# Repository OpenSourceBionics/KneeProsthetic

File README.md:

# KneeProsthetic

Passive and powered leg prostheses are expensive and require access to specific equipment and technology, making them very inaccessible. Our objective is to build an open source powered prosthesis that is lightweight, inexpensive, and has a functional controller to be a foundation for striving engineers.

## Getting Started

This repository contains the preliminary code to manually control your powered prosthesis through both wired and wireless communication. 

### Prerequisites

* Arduino - latest edition
* Teensyduino - latest edition
* Python 2.7

* Raspberry Pi Zero W (x2 for wireless communication)
* Teensy 4.0

### Installing

* [Teensyduino Download Link](https://www.pjrc.com/teensy/td_download.html)
* [Arduino Download Link](https://www.arduino.cc/en/main/software)

## Running the tests

Explain how to run the  tests for this system

## Authors

* **Justin Francis** - *Initial work* - [jphran](https://github.com/jphran)
* **Palani Thangaraj** - *Initial work* - [palan-thangaraj](https://github.com/palani-thangaraj)

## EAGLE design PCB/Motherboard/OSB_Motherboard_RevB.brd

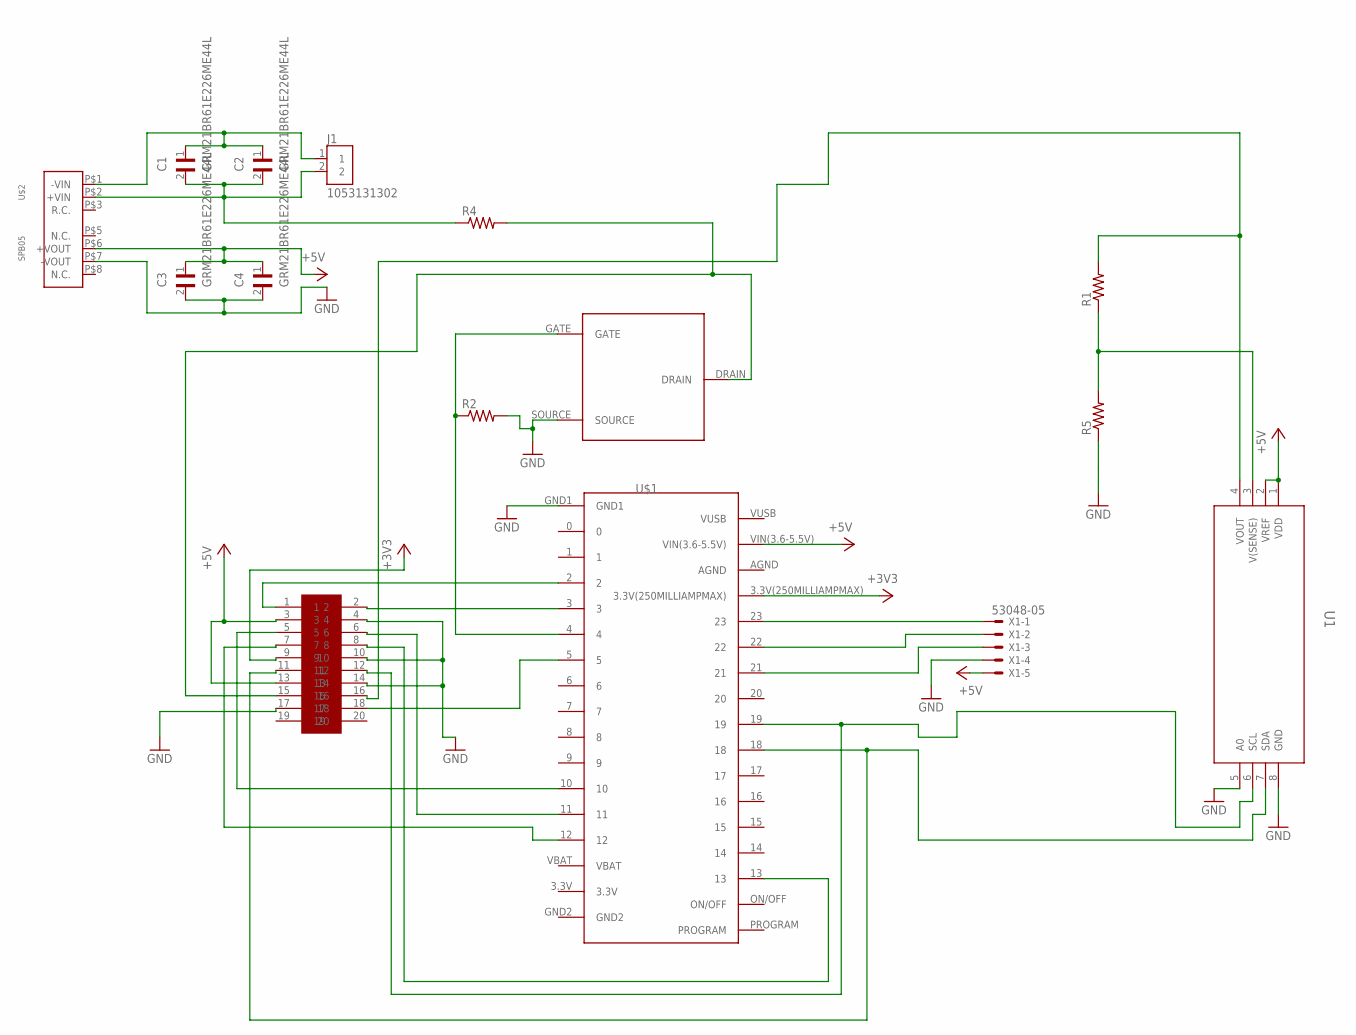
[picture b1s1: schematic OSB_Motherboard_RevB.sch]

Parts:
C1, C2, C3, C4: GRM21BR61E226ME44L; CAPC2012X135N
J1: 1053131302; MOLEX_1053131302
R1, R2, R4, R5: R-US_R0603; R0603
U1: DAC8571IDGKR; DGK8
U$1: TEENSEY4.0
U$2: SPB05; SPB05B-05
U$3: MGSF1N02L
U$4: MOLEX-PICOCLASP-2CIR
X1: 53048-05

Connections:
+3V3: U$1.3.3V(250MILLIAMPMAX), U$4.9
+5V: C3.1, C4.1, U1.1 (VDD), U1.2 (VREF), U$1.VIN(3.6-5.5V), U$2.P$6 (+VOUT), U$4.3, U$4.13, X1.5
GND: C3.2, C4.2, R2.2, R5.1, U1.5 (A0), U1.8 (GND), U$1.GND1, U$2.P$7 (-VOUT), U$3.SOURCE, U$4.4, U$4.10, U$4.14, U$4.17, X1.4
unnamed: U$1.2, U$4.1
unnamed: U$1.23, X1.1
unnamed: U1.6 (SCL), U$1.19, U$4.12
unnamed: U1.7 (SDA), U$1.18, U$4.11
unnamed: U$1.11, U$4.6
unnamed: U$1.3, U$4.2
unnamed: U$1.13, U$4.8
unnamed: U$1.22, X1.2
unnamed: U$1.21, X1.3
unnamed: U$1.12, U$4.7
unnamed: C1.1, C2.1, J1.1, U$2.P$1 (-VIN)
unnamed: U$1.10, U$4.5
unnamed: R1.1, R5.2, U1.3 (V(SENSE))
unnamed: R1.2, U1.4 (VOUT), U$4.16
unnamed: R2.1, U$1.4, U$3.GATE
unnamed: R4.2, U$3.DRAIN, U$4.15
unnamed: C1.2, C2.2, J1.2, R4.1, U$2.P$2 (+VIN)
unnamed: U$1.5, U$4.18

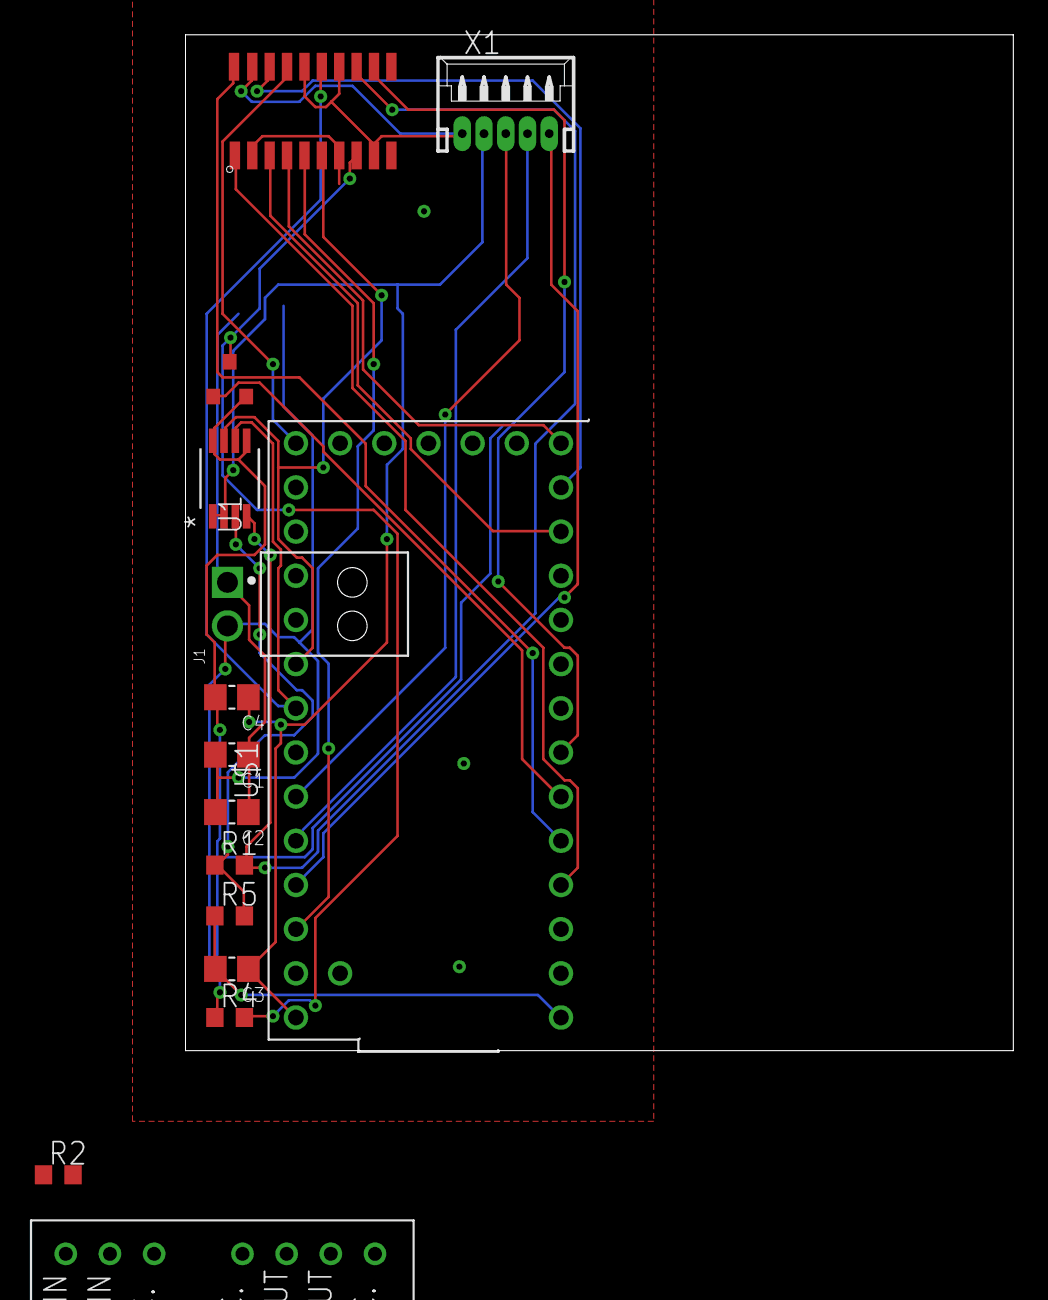
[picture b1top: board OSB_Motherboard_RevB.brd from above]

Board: 2 copper layers, 47.6 x 58.4 mm, 15 parts (0 on the bottom side), 21 nets.

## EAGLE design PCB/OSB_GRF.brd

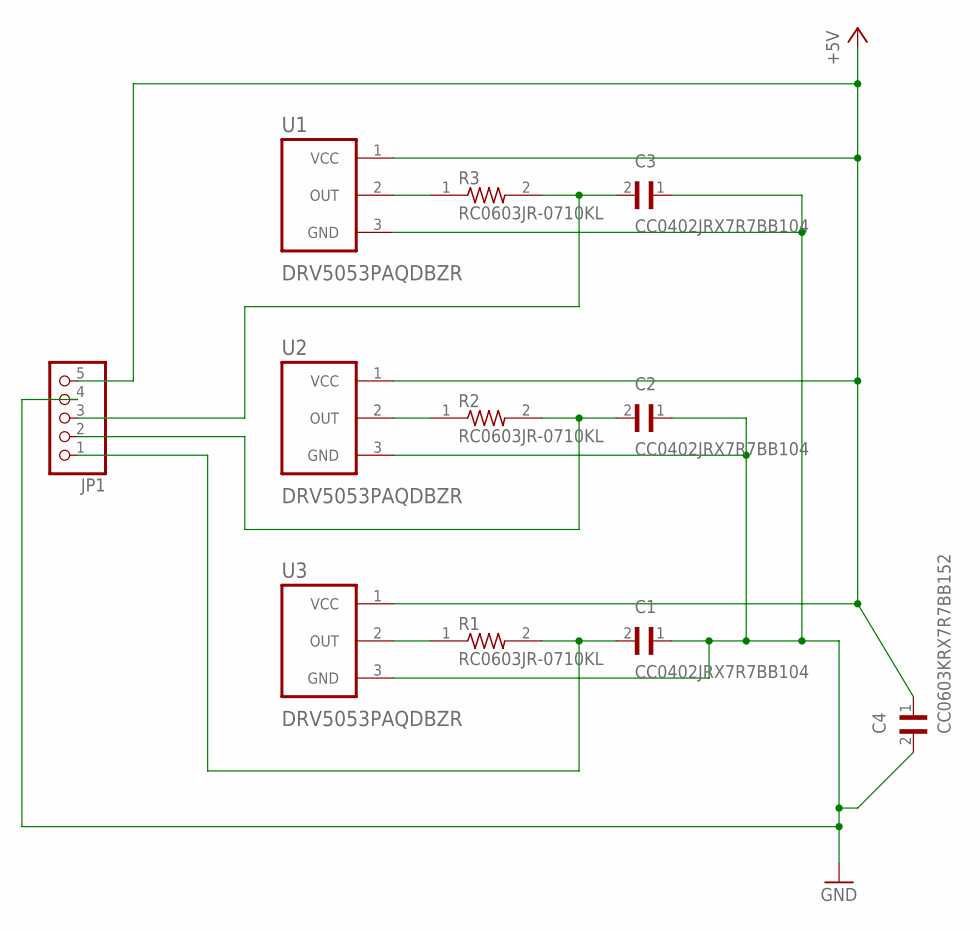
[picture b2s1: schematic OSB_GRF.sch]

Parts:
C1, C2, C3: CC0402JRX7R7BB104; CAPC1005X55N
C4: CC0603KRX7R7BB152; CAPC1608X90
JP1: PINHD-1X55X2MM; 1_05X2MM
R1, R2, R3: RC0603JR-0710KL; RESC1607X60N
U1, U2, U3: DRV5053PAQDBZR; SOT95P237X112-3N

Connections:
+5V: C4.1, JP1.5, U1.1 (VCC), U2.1 (VCC), U3.1 (VCC)
GND: C1.1, C2.1, C3.1, C4.2, JP1.4, U1.3 (GND), U2.3 (GND), U3.3 (GND)
unnamed: R1.1, U3.2 (OUT)
unnamed: R2.1, U2.2 (OUT)
unnamed: R3.1, U1.2 (OUT)
unnamed: C1.2, JP1.1, R1.2
unnamed: C2.2, JP1.2, R2.2
unnamed: C3.2, JP1.3, R3.2

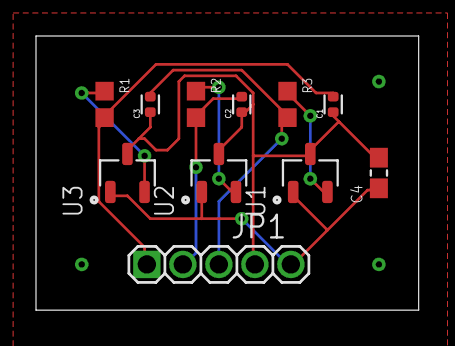
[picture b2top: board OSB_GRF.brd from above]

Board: 2 copper layers, 21.3 x 15.2 mm, 11 parts (0 on the bottom side), 8 nets.

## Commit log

2019-10-22 init
2019-10-24 modified class
2019-10-25 updated test file for motor lib
2019-10-29 added hall effect
2019-11-01 added int 3 hall effects
2019-11-01 merging in 3 hall sensors
2019-11-01 working, able to differnetiate bending vs shear
2019-11-04 added data logger
2019-11-04 added file name
2019-11-06 modified for teensy 3.6
2019-11-06 uploading log
2019-11-06 merging
2019-11-07 new data set
2019-11-07 working plotting script
2019-11-07 changed datalog names
2019-11-07 finalized plot for Dr Lenzi
2019-11-07 new weight shifting data
2019-11-07 added in last years janky code
2019-11-08 can't read the abs enc. need to try a new sensor
2019-11-09 update naming schema
2019-11-09 updating everything, but i left, so its kinda just everywhere.
2019-11-09 working on linking libs
2019-11-09 broken incEnc lib, cannot link to lib headers through #include
2019-11-10 working on integrating all senosors. code compiles
2019-11-11 added schematics
2019-11-12 finished OSB_GRF
2019-11-12 added in timing
2019-11-12 all sensors work, need to figure out libs
2019-11-14 added motherboard schematic
2019-11-14 working mpu 6050, last version was for mpu 9250
2019-11-15 added in motherboard RevB, working on motor char
2019-11-16 fixed motor.cpp
2019-11-17 added in motor char files, working on position p controller
2019-11-17 updated mtr fns
2019-11-17 added pd and pid controller, both are fairly unstable. need to tune. need to see if they're implemented correctly
2019-11-17 added step response files. need to do this again with the digital motor reset setup
2019-11-24 wireless communication code
2019-11-25 added in DAC verification code. does not work on mboard, need to probe i2c lines
2019-11-25 working hall effects, need to still figure out DAC
2019-11-26 working dac on teensy 3.2, working motherboard with 3.2
2019-11-27 p controllle for integration
2019-11-27 attempted walking with position p controller and pot... sheared shaft
2019-11-29 finialized pcb fil files
2019-11-30 fixed testingPcontroller
2019-11-30 fixed syntax in testingPcontroller
2019-12-01 spelling errors in testingPcontroller
2019-12-10 fixed motor command limitation voltage
2020-01-21 comments
2020-02-05 added potControll with abs enc
2020-02-10 working potController
2020-02-10 constrained abs enc
2020-02-10 fixed abs enc constraint
2020-02-14 working pot controller, implementing makita lib
2020-02-14 working pot controller
2020-02-20 Add files via upload
    These are the libraries for the motherboard revision A
2020-02-20 working on motherboard Rev B
2020-02-22 building finite state machine
2020-03-07 working on finite state machine
2020-03-25 added in trajectory eqn and finished state machine
2020-05-13 motor move
